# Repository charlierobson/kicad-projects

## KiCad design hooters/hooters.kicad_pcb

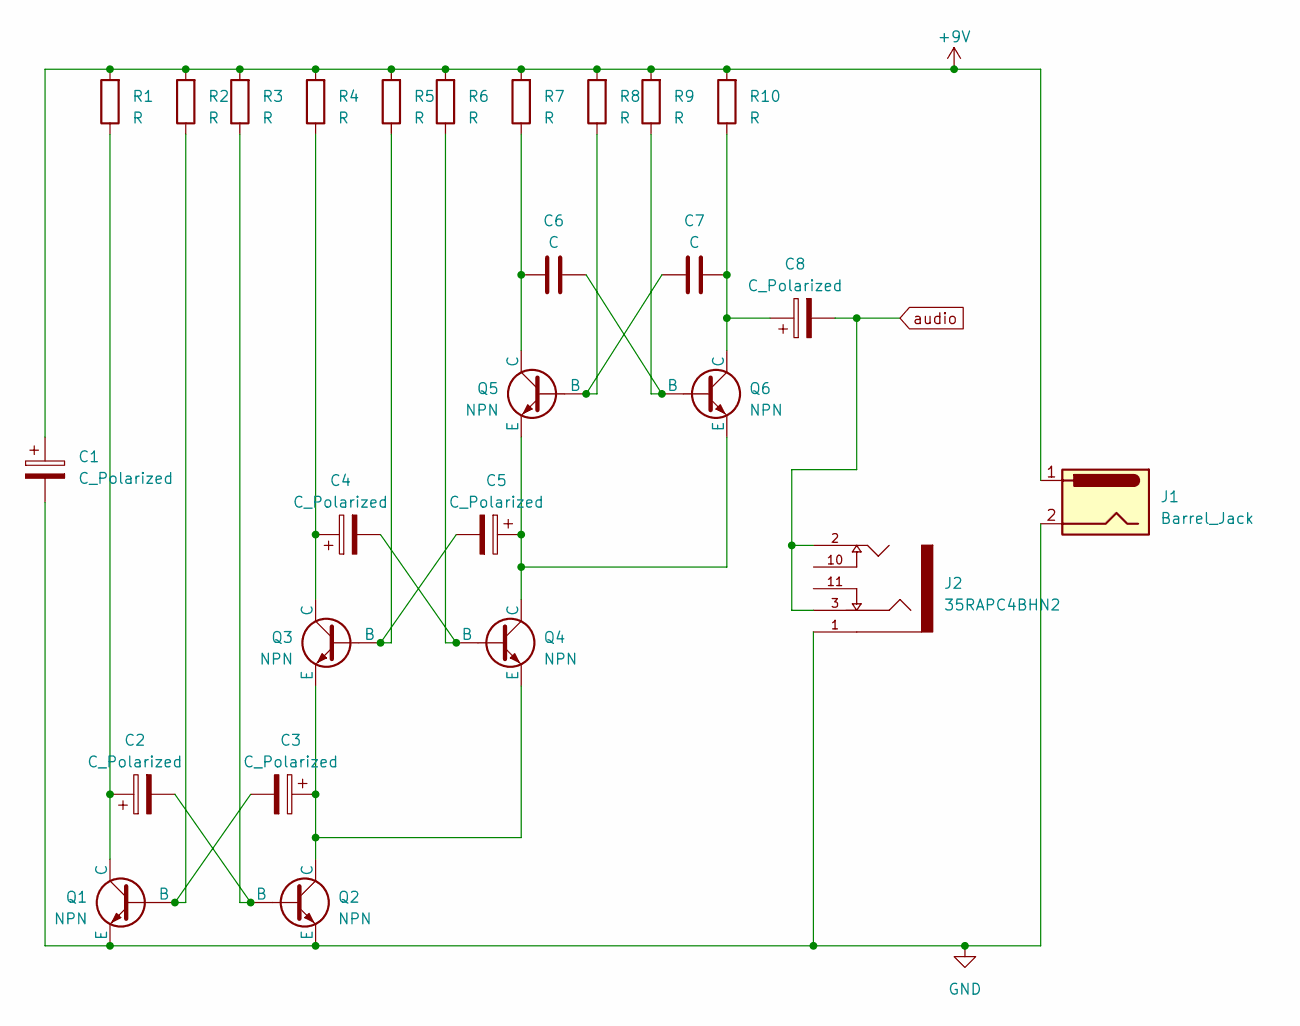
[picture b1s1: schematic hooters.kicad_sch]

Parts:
C1, C2, C3, C4, C5, C8: C_Polarized; CP_Radial_D4.0mm_P1.50mm
C6, C7: C; C_Disc_D3.0mm_W1.6mm_P2.50mm
J1: Barrel_Jack; BarrelJack_Horizontal
J2: 35RAPC4BHN2; SWITCHCRAFT_35RAPC4BHN2
Q1, Q2, Q3, Q4, Q5, Q6: NPN; TO-92L_HandSolder
R1, R2, R3, R4, R5, R6, R7, R8, R9, R10: R; R_Axial_DIN0207_L6.3mm_D2.5mm_P10.16mm_Horizontal

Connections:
+9V: C1.1, J1.1, R1.2, R2.2, R3.2, R4.2, R5.2, R6.2, R7.2, R8.2, R9.2, R10.2
GND: C1.2, J1.2, J2.1, Q1.3 (E), Q2.3 (E)
unnamed: C3.2, Q1.2 (B), R2.1
unnamed: C2.1, Q1.1 (C), R1.1
unnamed: C2.2, Q2.2 (B), R3.1
unnamed: C3.1, Q2.1 (C), Q3.3 (E), Q4.3 (E)
unnamed: C5.2, Q3.2 (B), R5.1
unnamed: C4.1, Q3.1 (C), R4.1
unnamed: C4.2, Q4.2 (B), R6.1
unnamed: C5.1, Q4.1 (C), Q5.3 (E), Q6.3 (E)
unnamed: C7.1, Q5.2 (B), R8.1
unnamed: C6.1, Q5.1 (C), R7.1
unnamed: C6.2, Q6.2 (B), R9.1
unnamed: C7.2, C8.1, Q6.1 (C), R10.1
audio: C8.2, J2.2, J2.3

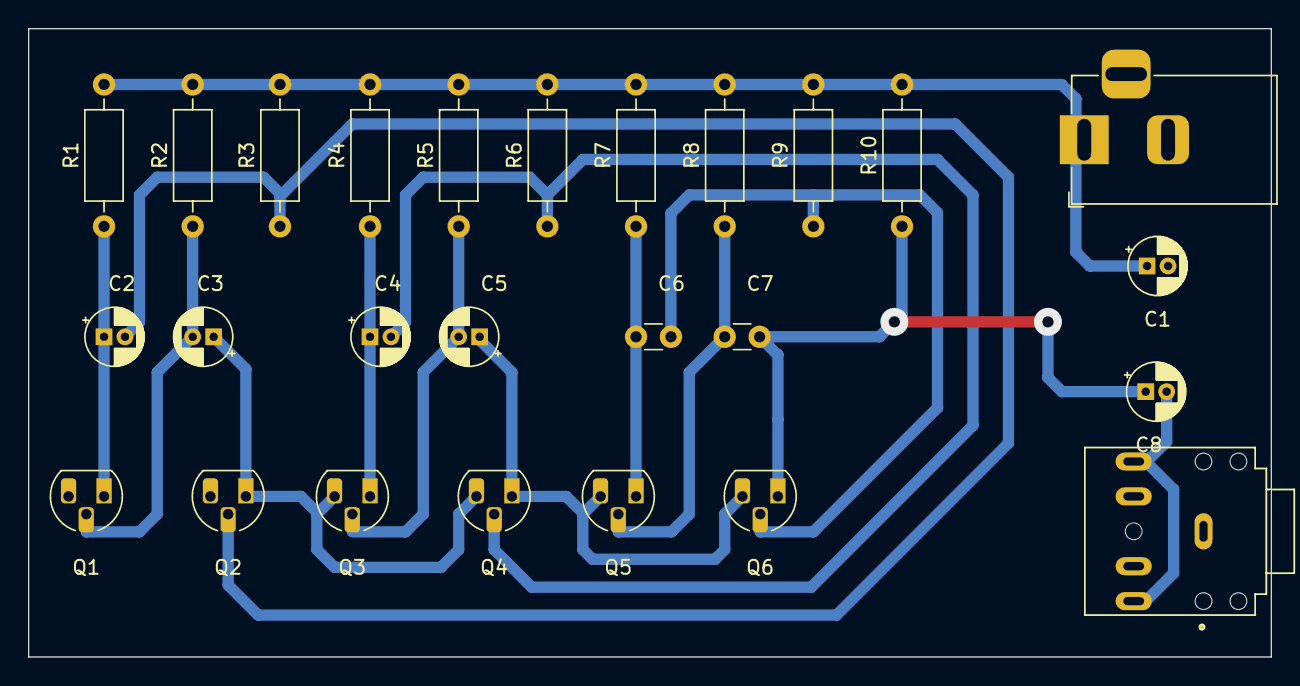
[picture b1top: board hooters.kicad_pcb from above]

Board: 2 copper layers, 89.0 x 45.0 mm, 26 parts (0 on the bottom side), 15 nets.

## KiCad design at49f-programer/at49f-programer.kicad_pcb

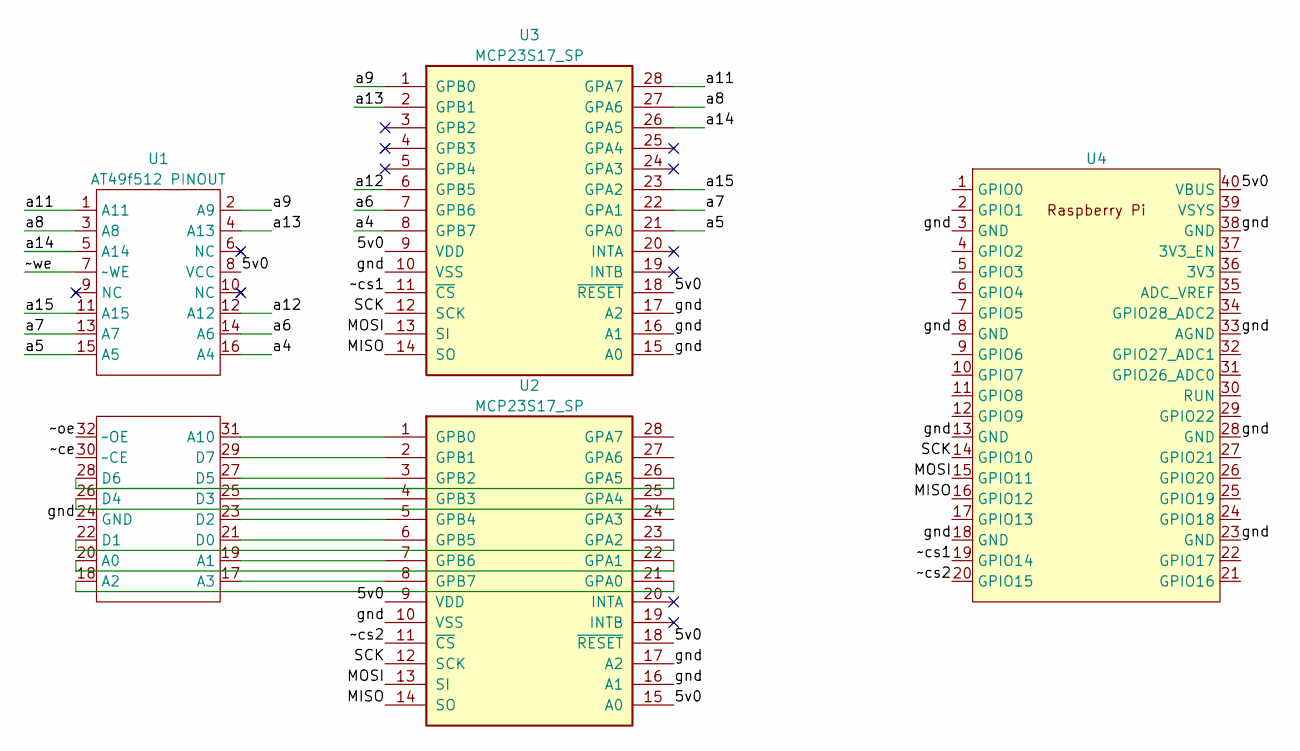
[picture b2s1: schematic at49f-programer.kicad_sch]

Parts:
U1: AT49f512 PINOUT; adapter-32-pin
U2, U3: MCP23S17_SP; DIP-28_W7.62mm
U4: pico-th

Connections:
/5v0: U1.8 (VCC), U2.9 (VDD), U2.15 (A0), U2.18 (~RESET), U3.9 (VDD), U3.18 (~RESET), U4.40 (VBUS)
/MISO: U2.14 (SO), U3.14 (SO), U4.16 (GPIO12)
/MOSI: U2.13 (SI), U3.13 (SI), U4.15 (GPIO11)
/SCK: U2.12 (SCK), U3.12 (SCK), U4.14 (GPIO10)
/a4: U1.16 (A4), U3.8 (GPB7)
/a5: U1.15 (A5), U3.21 (GPA0)
/a6: U1.14 (A6), U3.7 (GPB6)
/a7: U1.13 (A7), U3.22 (GPA1)
/a8: U1.3 (A8), U3.27 (GPA6)
/a9: U1.2 (A9), U3.1 (GPB0)
/a11: U1.1 (A11), U3.28 (GPA7)
/a12: U1.12 (A12), U3.6 (GPB5)
/a13: U1.4 (A13), U3.2 (GPB1)
/a14: U1.5 (A14), U3.26 (GPA5)
/a15: U1.11 (A15), U3.23 (GPA2)
/gnd: U1.24 (GND), U2.10 (VSS), U2.16 (A1), U2.17 (A2), U3.10 (VSS), U3.15 (A0), U3.16 (A1), U3.17 (A2), U4.3 (GND), U4.8 (GND), U4.13 (GND), U4.18 (GND), U4.23 (GND), U4.28 (GND), U4.33 (AGND), U4.38 (GND)
/~ce: U1.30 (~CE)
/~cs1: U3.11 (~CS), U4.19 (GPIO14)
/~cs2: U2.11 (~CS), U4.20 (GPIO15)
/~oe: U1.32 (~OE)
/~we: U1.7 (~WE)
unnamed: U1.20 (A0), U2.22 (GPA1)
unnamed: U1.19 (A1), U2.7 (GPB6)
unnamed: U1.18 (A2), U2.21 (GPA0)
unnamed: U1.17 (A3), U2.8 (GPB7)
unnamed: U1.31 (A10), U2.1 (GPB0)
unnamed: U1.21 (D0), U2.6 (GPB5)
unnamed: U1.22 (D1), U2.23 (GPA2)
unnamed: U1.23 (D2), U2.5 (GPB4)
unnamed: U1.25 (D3), U2.4 (GPB3)
unnamed: U1.26 (D4), U2.25 (GPA4)
unnamed: U1.27 (D5), U2.3 (GPB2)
unnamed: U1.28 (D6), U2.26 (GPA5)
unnamed: U1.29 (D7), U2.2 (GPB1)

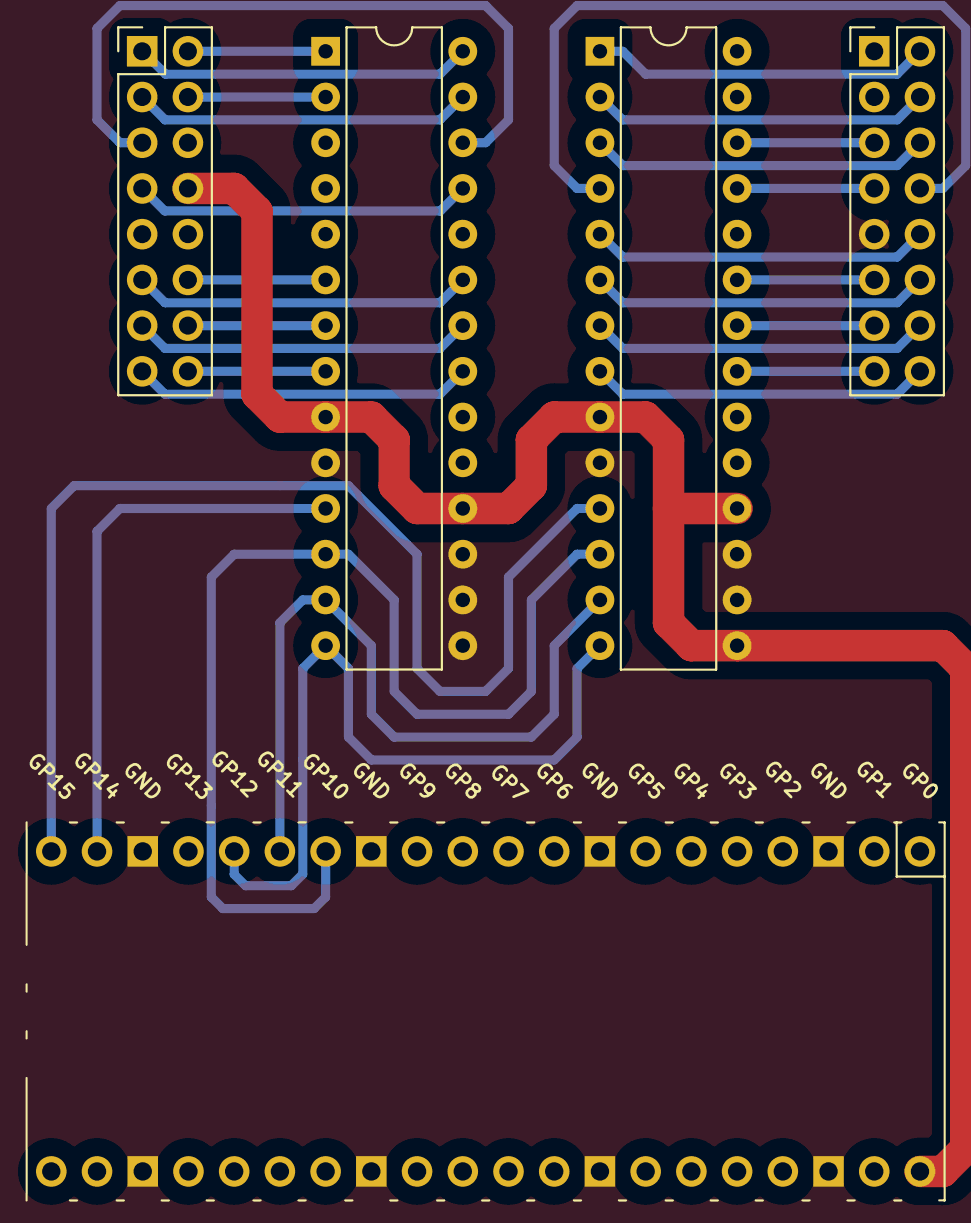
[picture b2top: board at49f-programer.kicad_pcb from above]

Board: 2 copper layers, 4 parts (0 on the bottom side), 31 nets.

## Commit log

2023-02-21 adding pico
2023-03-01 add hooters
